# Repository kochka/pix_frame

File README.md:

# pix-frame

A 16×16 pixel art frame that plays retro animations, with the time, the
weather and the room temperature in between. It runs on an ESP32-C6 with a
firmware written in Rust.

▶️ **[Watch the demo on YouTube](https://www.youtube.com/watch?v=8LqMPComf-A)**

## What it does

- Plays your pixel art animations in random order, without showing the same
  one again too soon.
- Every few animations, shows an information screen:
  - the time, set from the internet;
  - the outdoor weather, with an icon and the temperature;
  - the room temperature and humidity.
- Follows the light in the room, dimmer in the evening and brighter in
  daylight.
- Works without Wi-Fi too: it then only plays animations and shows the
  indoor screens.

Everything is in this repository: the firmware, the PC tools, the carrier
board (KiCad) and the 3D-printed rear structure.

## How it works

Animations are authored in the usual formats (GIF, APNG, WebP, PNG), converted
on a PC into a small purpose-built binary format called **PXA**, and streamed
by the firmware from flash with a fixed, predictable memory footprint. The
ESP32 never decodes GIF or PNG.

```text
GIF / APNG / WebP / PNG
          │
          ▼
   pxa convert (PC)
          │
          ▼
    animation.pxa
          │
          ▼
    pxa bundle (PC)  ──►  animations partition  ──►  ESP32-C6 firmware  ──►  WS2815 LED matrix
```

## Hardware

The current frame is:

- an ESP32-C6-WROOM-1-N8 module (8 MB flash, Wi-Fi);
- a 16×16 WS2815 12 V LED matrix, wired as a single serpentine chain;
- the LED data line on GPIO18 (SPI with DMA), driven directly at 3.3 V;
- a MINI560 buck converter supplying 5 V to the ESP32 side;
- an SHT3x temperature and humidity sensor on I2C;
- a GL5528 photoresistor for the ambient light;
- a push button that runs the LED self-test.

The 16×16 size is a configuration, not a limit. Matrix dimensions and wiring
are declared in one place in the firmware and the file format is dimension
agnostic. See the [hardware reference](doc/wiring.md) for the circuit,
external wiring, carrier PCB and assembly instructions, and
[`hardware/mechanical`](hardware/mechanical/) for the printed parts.

## Repository layout

| Path | Contents |
| --- | --- |
| `crates/pxa-core` | `no_std`, allocation-free implementation of the PXA format, shared by the firmware and the converter |
| `firmware` | ESP32-C6 application built on `esp-hal` |
| `tools/pxa` | Desktop CLI that converts animations to PXA, bundles them and inspects PXA files |
| `tools/pixframe` | Desktop CLI that builds the device configuration image |
| `config.example.toml` | Template for the device configuration |
| `partitions.csv` | Flash partition table: firmware, reserved OTA space, `animations` data partition |
| `doc/PXA_spec.md` | Authoritative specification of the PXA binary format |
| `doc/wiring.md` | Hardware reference: circuit, wiring, PCB, assembly and commissioning |
| `hardware` | KiCad 10 project for the carrier board, and the 3D-printed rear structure in `hardware/mechanical` |

## The PXA format in short

A PXA v1 file is a 16-byte header, a global RGB888 palette of 1 to 256 colors,
then one 8-byte header and one payload per frame. Pixels are palette indices
packed at 1, 2, 4 or 8 bits per pixel depending only on the palette size.
Every frame is complete and has its own duration. There is no compression,
no transparency and no metadata, which keeps the decoder tiny.

A 16×16 animation with 16 colors costs 136 bytes per frame. Five seconds at
20 FPS is about 13 KiB.

Full details, byte layouts and validation rules are in
[`doc/PXA_spec.md`](doc/PXA_spec.md).

## Building

Requirements: a stable Rust toolchain (pinned by `rust-toolchain.toml`, which
also pulls the `riscv32imac-unknown-none-elf` target), and
[`espflash`](https://github.com/esp-rs/espflash) to flash the board.
[`mise`](https://mise.jdx.dev/) is optional but provides the canonical tasks.

Host-side checks (format, tests, lints, converter build):

```bash
mise run check
```

Or with plain Cargo:

```bash
cargo test -p pxa-core -p pxa
cargo clippy -p pxa-core -p pxa --all-targets -- -D warnings
cargo build -p pxa --release
```

Firmware:

```bash
mise run build-firmware
# or
cargo build -p pix-frame-firmware --release --target riscv32imac-unknown-none-elf
```

Flash and open the serial monitor. The `espflash` runner in
`.cargo/config.toml` applies `partitions.csv`, so run this from the workspace
root:

```bash
mise run flash
# or
cargo run -p pix-frame-firmware --release --target riscv32imac-unknown-none-elf
```

A plain `cargo build` at the workspace root only builds the host packages; the
firmware always needs the explicit `-p` and `--target`.

### Loading animations onto the frame

Animations live in the `animations` partition, separate from the firmware,
as a bundle of PXA files (see the spec, section 4). Put your `.pxa` files in
`assets/` (ignored by git) and run:

```bash
mise run flash-assets
```

This builds the bundle with `pxa bundle assets/*.pxa -o target/animations.bin`,
erases the partition and writes the image at its offset with `espflash`.
Reflashing the firmware does not touch the animations, and vice versa.

### Configuring the frame

Optional features (information screens, Wi-Fi, clock, weather, ambient
light, display settings) are driven by a configuration stored in the `nvs` partition. Copy
`config.example.toml` to `config.toml` (ignored by git, it holds the Wi-Fi
password), edit it, then:

```bash
mise run flash-config
```

This runs `pixframe config build config.toml -o target/nvs.bin` and writes the
image at the partition offset. `pixframe config dump target/nvs.bin` prints
what an image contains, without the password. A frame without configuration
just plays animations.

### Firmware behavior

At boot the firmware reads the partition table, indexes the bundle (up to 256
animations) and logs what it found over the serial port, including a warning
when indexing stopped before the end of the bundle. It then plays in a
random order: each cycle is a shuffle of every animation, and the first third
of a new cycle never repeats the last third of the previous one, so at least
a third of the catalog plays between two showings of the same animation. An animation loops until at least
`min_play_seconds` (3 by default) have been scheduled at a loop boundary, so short loops repeat and long
ones play once in full.

Frames are scheduled on cumulative deadlines from the first frame: the next
frame is decoded while the current one is displayed, then sent when its
predecessor's duration has elapsed. Decoding and LED transmission time do not
accumulate as drift. A late frame is shown as soon as it is ready and the
schedule is not rebased.

Pressing the BOOT button of the dev board (GPIO9) runs the LED self-test once,
after which playback resumes with the next animation. The self-test ends with
a preview of every screen: text, clock, the seven weather icons in quick
succession, the indoor temperature and humidity screens, and the Wi-Fi
status.

With a `[wifi]` section in the configuration, the firmware joins the network
at boot and keeps reconnecting after drops. The first result is flashed on the
matrix for a moment ("WIFI" then "OK" in green or "KO" in red), and the
self-test ends with the same screen. Once connected, the clock is set from
`pool.ntp.org` and refreshed every hour. The local offset comes from the
configured time zone: built-in rules cover the European Union and UTC, and
the weather service supplies the exact offset for any zone once it has
answered. Without Wi-Fi the frame only plays animations.

With a `[location]` section, the current outdoor conditions are fetched from
[Open-Meteo](https://open-meteo.com/) (free, no key, plain HTTP) every
15 minutes. The weather screen shows an icon for the sky condition (clear,
partly cloudy, cloudy, fog, rain, snow, thunderstorm) above the temperature
in whole degrees, colored from blue to red. It is skipped when the last
answer is older than an hour.

An SHT3x sensor on I2C (SDA on GPIO6, SCL on GPIO7, see `doc/wiring.md`
section 8) is read every minute. Two screens show it: a thermometer above
the temperature, to the tenth of a degree, and a drop above the relative
humidity. They need neither Wi-Fi nor the clock, and are skipped when no
reading succeeded in the last 5 minutes, so a frame without the sensor simply
never shows them.

A GL5528 photoresistor on GPIO2 (see `doc/wiring.md` section 7) is sampled
continuously and its voltage logged every 10 seconds. With a `[light]`
section, the brightness follows the room: the voltage is mapped linearly from
`dark_mv..bright_mv` onto `min_brightness..max_brightness`, and the matrix
moves towards the new value one level every 25 ms instead of jumping. Read
the two thresholds from the logs with the frame assembled in its place: one
in the evening light where the frame should be at its dimmest, one in the
light where it should be at its brightest. Without the section the brightness
stays fixed.

When `info_every` is set, an information screen is shown for 5 seconds after
that many animations. Each screen has an availability condition, so it is
skipped until its data exists: the clock waits for the first time sync, the
weather for the first Open-Meteo answer, the indoor screens for the first
sensor reading. Available screens alternate. Hours are drawn above minutes in
large bold digits, pink above cyan unless `[clock]` sets other colors, with
a separator blinking every second between them. Temperatures are shown in
Celsius, or in Fahrenheit with `temperature_unit = "F"`.

Files whose dimensions differ from the matrix, or that fail validation, are
logged and skipped. Without any playable animation the LED self-test runs
instead. The fixed brightness is a constant at the top of `firmware/src/main.rs`.

## Using the `pxa` converter

The binary is produced at `target/release/pxa`. It has four commands.

### `pxa convert`

Converts one or more source animations to PXA. Supported inputs: GIF, PNG,
APNG and WebP. Each output takes the input's name with a `.pxa` extension.

```bash
pxa convert cat.gif
```

```text
cat.gif -> cat.pxa: 16x16, 12 frames, 9 colors (4 bpp), 1675 bytes
```

Several inputs are converted in turn. A file that fails is reported and
skipped, the others are still written, and the exit status is non-zero. Inputs
that would share an output name, such as `cat.gif` and `cat.png`, are rejected
up front:

```bash
pxa convert *.gif -o animations/
```

Options:

| Option | Effect |
| --- | --- |
| `-o, --output PATH` | Output file for a single input, or an existing directory for any number of inputs. Default: next to each input. |
| `--size WxH` | Resize with nearest-neighbour sampling, e.g. `--size 16x16`. By default the source dimensions are kept. |
| `--background RRGGBB` | Color composited under transparent pixels. Default `000000` (black). |
| `--default-duration MS` | Duration given to source frames whose delay is zero, and to static images. Without it, zero-delay frames are omitted. |
| `--colors N` | Maximum palette size, 1 to 256. Sources with more colors are quantized. Default 256. |

The converter keeps the exact source colors whenever the whole animation fits
the palette, which is the case for almost all pixel art. Quantization only
happens when it must, and a note is printed when it does.

Typical cases:

```bash
# 32×32 source scaled down to the frame, transparent areas over dark grey
pxa convert ghost.png --size 16x16 --background 202020

# Old GIF where every frame has a delay of 0: keep the frames at 100 ms each
pxa convert old.gif --default-duration 100

# Force a 16-color palette (4 bpp) to halve the file size
pxa convert photo.webp --colors 16 -o /tmp/photo16.pxa
```

Two conversions of the same input with the same options produce identical
files.

### `pxa inspect`

Prints the header, the palette and every frame with its duration.

```bash
pxa inspect cat.pxa
```

```text
file:        cat.pxa (439 bytes)
magic:       PXA1
size:        16x16
frames:      3
palette:     5 colors
depth:       4 bpp
payload:     128 bytes per frame
expected:    439 bytes
palette:
    0: #FF0000
    1: #000000
    ...
frames:
     0:   100 ms, 128 payload bytes
     1:   200 ms, 128 payload bytes
     2:    50 ms, 128 payload bytes
total:       350 ms per loop
```

### `pxa bundle`

Validates PXA files and concatenates them, in the given order, into the raw
image expected by the `animations` partition. The image ends with a four-byte
marker so the firmware stops at the last file even if the partition previously
held a larger bundle. Any invalid input aborts the bundle. Files whose dimensions differ from the
rest of the bundle are reported, since the firmware skips them.

```bash
pxa bundle assets/*.pxa -o animations.bin
```

```text
0x000000     3871 bytes  16x16, 14 frames  assets/batman.pxa
0x000f1f      581 bytes  16x16, 4 frames  assets/bissie.pxa
animations.bin: 2 animations, 4456 bytes
```

Write it to the frame with `mise run flash-assets`, or by hand:

```bash
espflash erase-region --chip esp32c6 0x410000 0x3F0000
espflash write-bin --chip esp32c6 0x410000 animations.bin
```

### `pxa validate`

Checks that a file is a conforming PXA v1 file and exits with a non-zero
status otherwise. Errors name the frame and the field at fault.

```bash
pxa validate cat.pxa
```

```text
cat.pxa: valid PXA v1, 16x16, 3 frames, 5 colors
```

```text
error: broken.pxa: invalid PXA file: frame 2: pixel 17 uses palette index 9, outside the palette
```

## Status

Done:

- PXA v1 specification;
- `pxa-core` encoder, decoder and validation, with byte-exact tests;
- `pxa` converter with `convert` (single or bulk), `bundle`, `inspect` and `validate`;
- firmware PXA player streaming from a dedicated flash partition, random
  playlist with a minimum play time;
- firmware LED self-test with a configurable matrix layout;
- device configuration in NVS with the `pixframe` tool;
- Wi-Fi station, SNTP time synchronisation, clock, outdoor weather and indoor
  temperature and humidity screens shown every N animations.

Not yet:

- `pxa preview`;
- Aseprite and Divoom importers;
- uploading animations to the frame without reflashing.

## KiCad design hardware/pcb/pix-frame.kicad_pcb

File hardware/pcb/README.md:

# Carrier PCB

KiCad 10 project for the pix-frame revision A carrier: **54 × 145 mm**, two
copper layers, **1.6 mm** board thickness. The Waveshare ESP32-C6-DEV-KIT-N8
mounts directly by its castellations. The carrier includes an IRF4905 high-side
switch, MINI560 5 V converter, 1N5819 isolation diode, flat-tab DC jack and
matrix/sensor/switch wire-solder pads. C1 and Q1 mount horizontally.

The [hardware reference](../../doc/wiring.md) documents component values,
pad assignments, module polarities, mechanical dimensions and commissioning.

Open the project from the repository root:

```bash
kicad hardware/pcb/pix-frame.kicad_pro
```

| File | Contents |
| --- | --- |
| `pix-frame.kicad_sch` | Electrical schematic |
| `pix-frame.kicad_pcb` | Routed carrier with filled GND planes |
| `pix-frame.kicad_pro` | Net classes and design rules |
| `pixframe.kicad_sym` | Devkit and MINI560 symbols |
| `pixframe.pretty/` | Module, horizontal capacitor, DC jack and wire-pad footprints |
| `pixframe.3dshapes/` | Component models for the KiCad 3D viewer |
| `fp-lib-table`, `sym-lib-table` | Project-local library registrations using `${KIPRJMOD}` |

Generated review files belong in `target/pcb/revA/` at the repository root.
Fabrication outputs belong in `hardware/pcb/production/`. Both directories,
local editor state and backups are ignored by Git. Refill zones, save and
run ERC/DRC with schematic parity before regenerating outputs.

Printable parts and their CAD sources belong in [../mechanical/](../mechanical/).

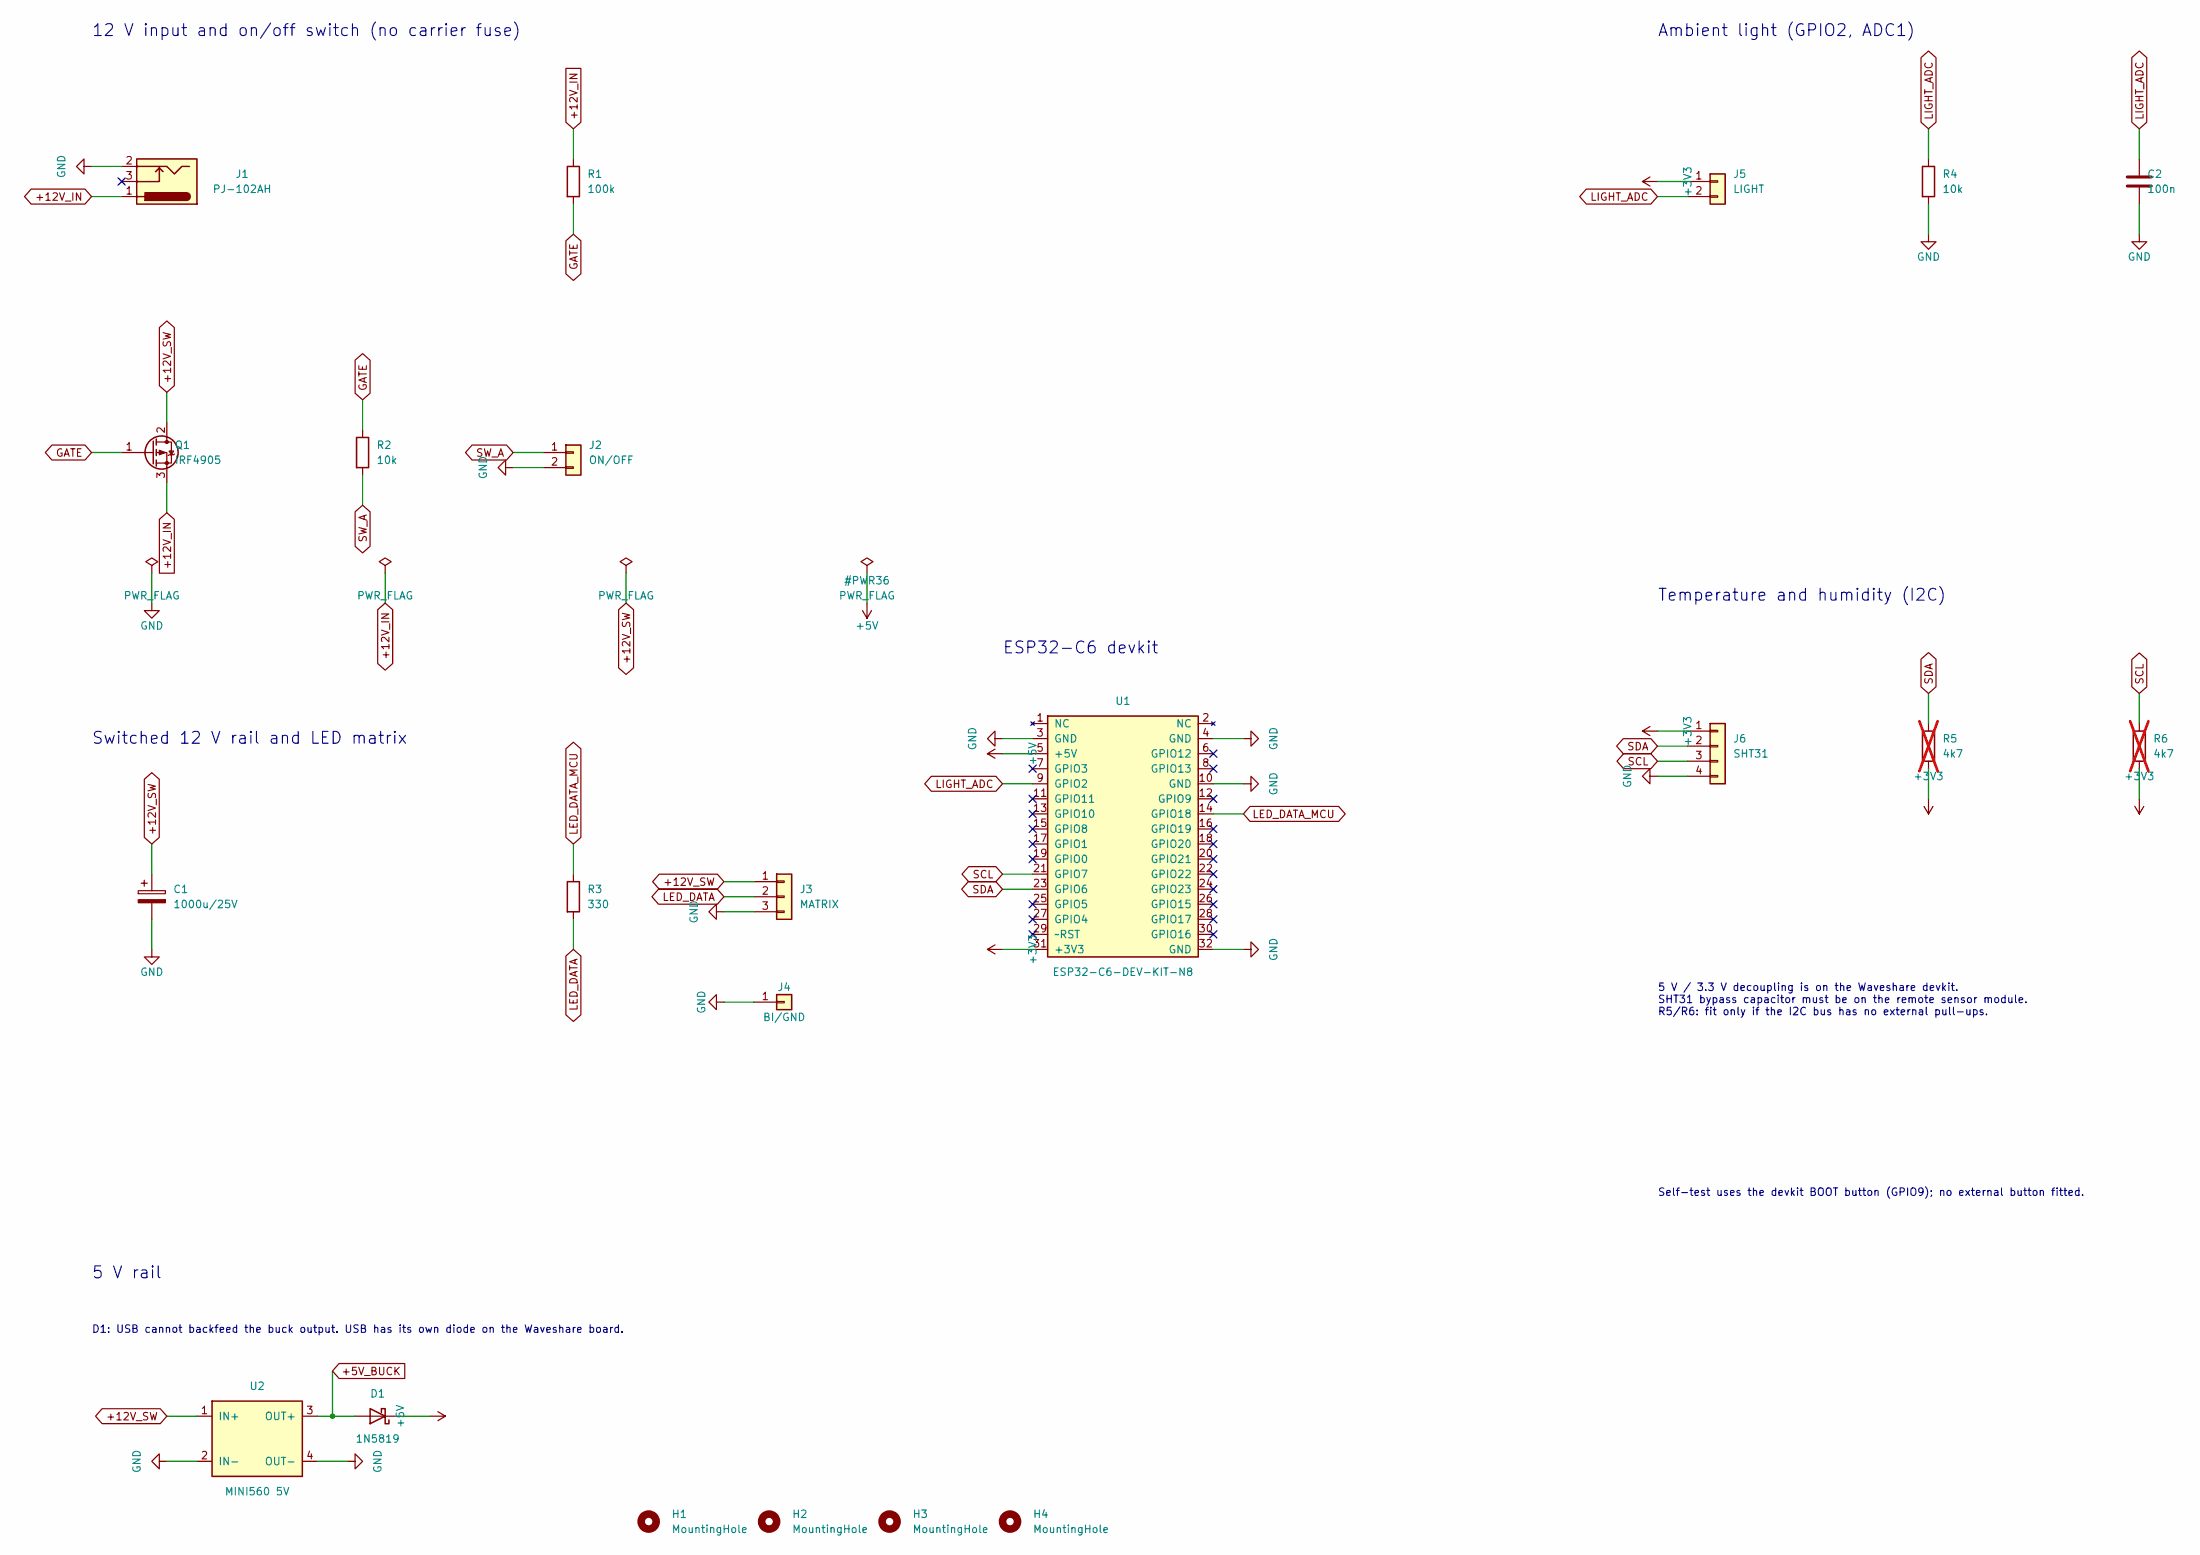
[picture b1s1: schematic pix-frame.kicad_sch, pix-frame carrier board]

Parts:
C1: 1000u/25V; CP_Radial_D10.5mm_L26mm_P5.00mm_Horizontal
C2: 100n; C_Disc_D5.0mm_W2.5mm_P5.00mm
D1: 1N5819; D_DO-41_SOD81_P10.16mm_Horizontal
H1, H2, H3, H4: MountingHole; MountingHole_3.2mm_M3
J1: PJ-102AH; BarrelJack_PJ102AH_Horizontal
J2: ON/OFF; WirePads_2_P4.00mm
J3: MATRIX; WirePads_Matrix_P6.00mm
J4: BI/GND; WirePad_D2.8mm_Drill1.1mm
J5: LIGHT; WirePads_2_P4.00mm
J6: SHT31; WirePads_4_P4.00mm
Q1: IRF4905; TO-220-3_Horizontal_TabUp
R1: 100k; R_Axial_DIN0207_L6.3mm_D2.5mm_P10.16mm_Horizontal
R2, R4: 10k; R_Axial_DIN0207_L6.3mm_D2.5mm_P10.16mm_Horizontal
R3: 330; R_Axial_DIN0207_L6.3mm_D2.5mm_P10.16mm_Horizontal
R5, R6: 4k7; R_Axial_DIN0207_L6.3mm_D2.5mm_P10.16mm_Horizontal; not fitted
U1: ESP32-C6-DEV-KIT-N8; ESP32-C6-DEV-KIT_Waveshare_Castellated
U2: MINI560 5V; MINI560_Buck_22.5x17mm_CornerLands

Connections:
+3V3: J5.1, J6.1, R5.2, R6.2, U1.31 (+3V3)
+5V: D1.1 (K), U1.5 (+5V)
+5V_BUCK: D1.2 (A), U2.3 (OUT+)
+12V_IN: J1.1, Q1.3 (S), R1.1
+12V_SW: C1.1, J3.1, Q1.2 (D), U2.1 (IN+)
GATE: Q1.1 (G), R1.2, R2.1
GND: C1.2, C2.2, J1.2, J2.2, J3.3, J4.1, J6.4, R4.2, U1.3 (GND), U1.4 (GND), U1.10 (GND), U1.32 (GND), U2.2 (IN-), U2.4 (OUT-)
LED_DATA: J3.2, R3.2
LED_DATA_MCU: R3.1, U1.14 (GPIO18)
LIGHT_ADC: C2.1, J5.2, R4.1, U1.9 (GPIO2)
SCL: J6.3, R6.1, U1.21 (GPIO7)
SDA: J6.2, R5.1, U1.23 (GPIO6)
SW_A: J2.1, R2.2

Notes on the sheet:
5 V rail
Switched 12 V rail and LED matrix
D1: USB cannot backfeed the buck output. USB has its own diode on the Waveshare board.
ESP32-C6 devkit
Self-test uses the devkit BOOT button (GPIO9); no external button fitted.
5 V / 3.3 V decoupling is on the Waveshare devkit. SHT31 bypass capacitor must be on the remote sensor module. R5/R6: fit only if the I2C bus has no external pull-ups.
Ambient light (GPIO2, ADC1)
Temperature and humidity (I2C)
12 V input and on/off switch (no carrier fuse)

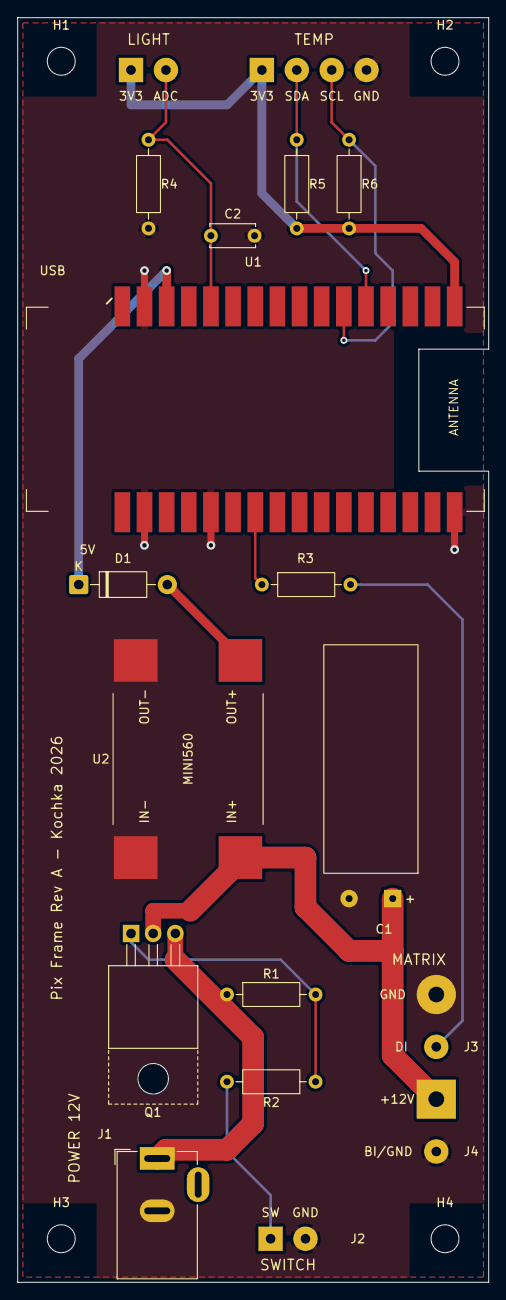
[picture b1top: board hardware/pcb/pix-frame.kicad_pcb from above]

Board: 2 copper layers, 54.0 x 145.0 mm, 22 parts (0 on the bottom side), 13 nets.

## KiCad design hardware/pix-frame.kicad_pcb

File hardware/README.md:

# Hardware

- [`pcb/`](pcb/): KiCad carrier-board project, symbols, footprints and component
  models for the PCB's 3D view.
- [`mechanical/`](mechanical/): CAD sources and printable parts for the frame and
  PCB support.

Open `hardware/pcb/pix-frame.kicad_pro` in KiCad from the workspace root.
See the [hardware reference](../doc/wiring.md) for the circuit, wiring,
carrier dimensions, assembly and commissioning.

Version the design sources and required project libraries. Generated review
files belong under `target/pcb/`; fabrication exports belong under
`hardware/pcb/production/`. Both output directories, local editor state,
backups and Fabrication Toolkit preferences are ignored by Git.

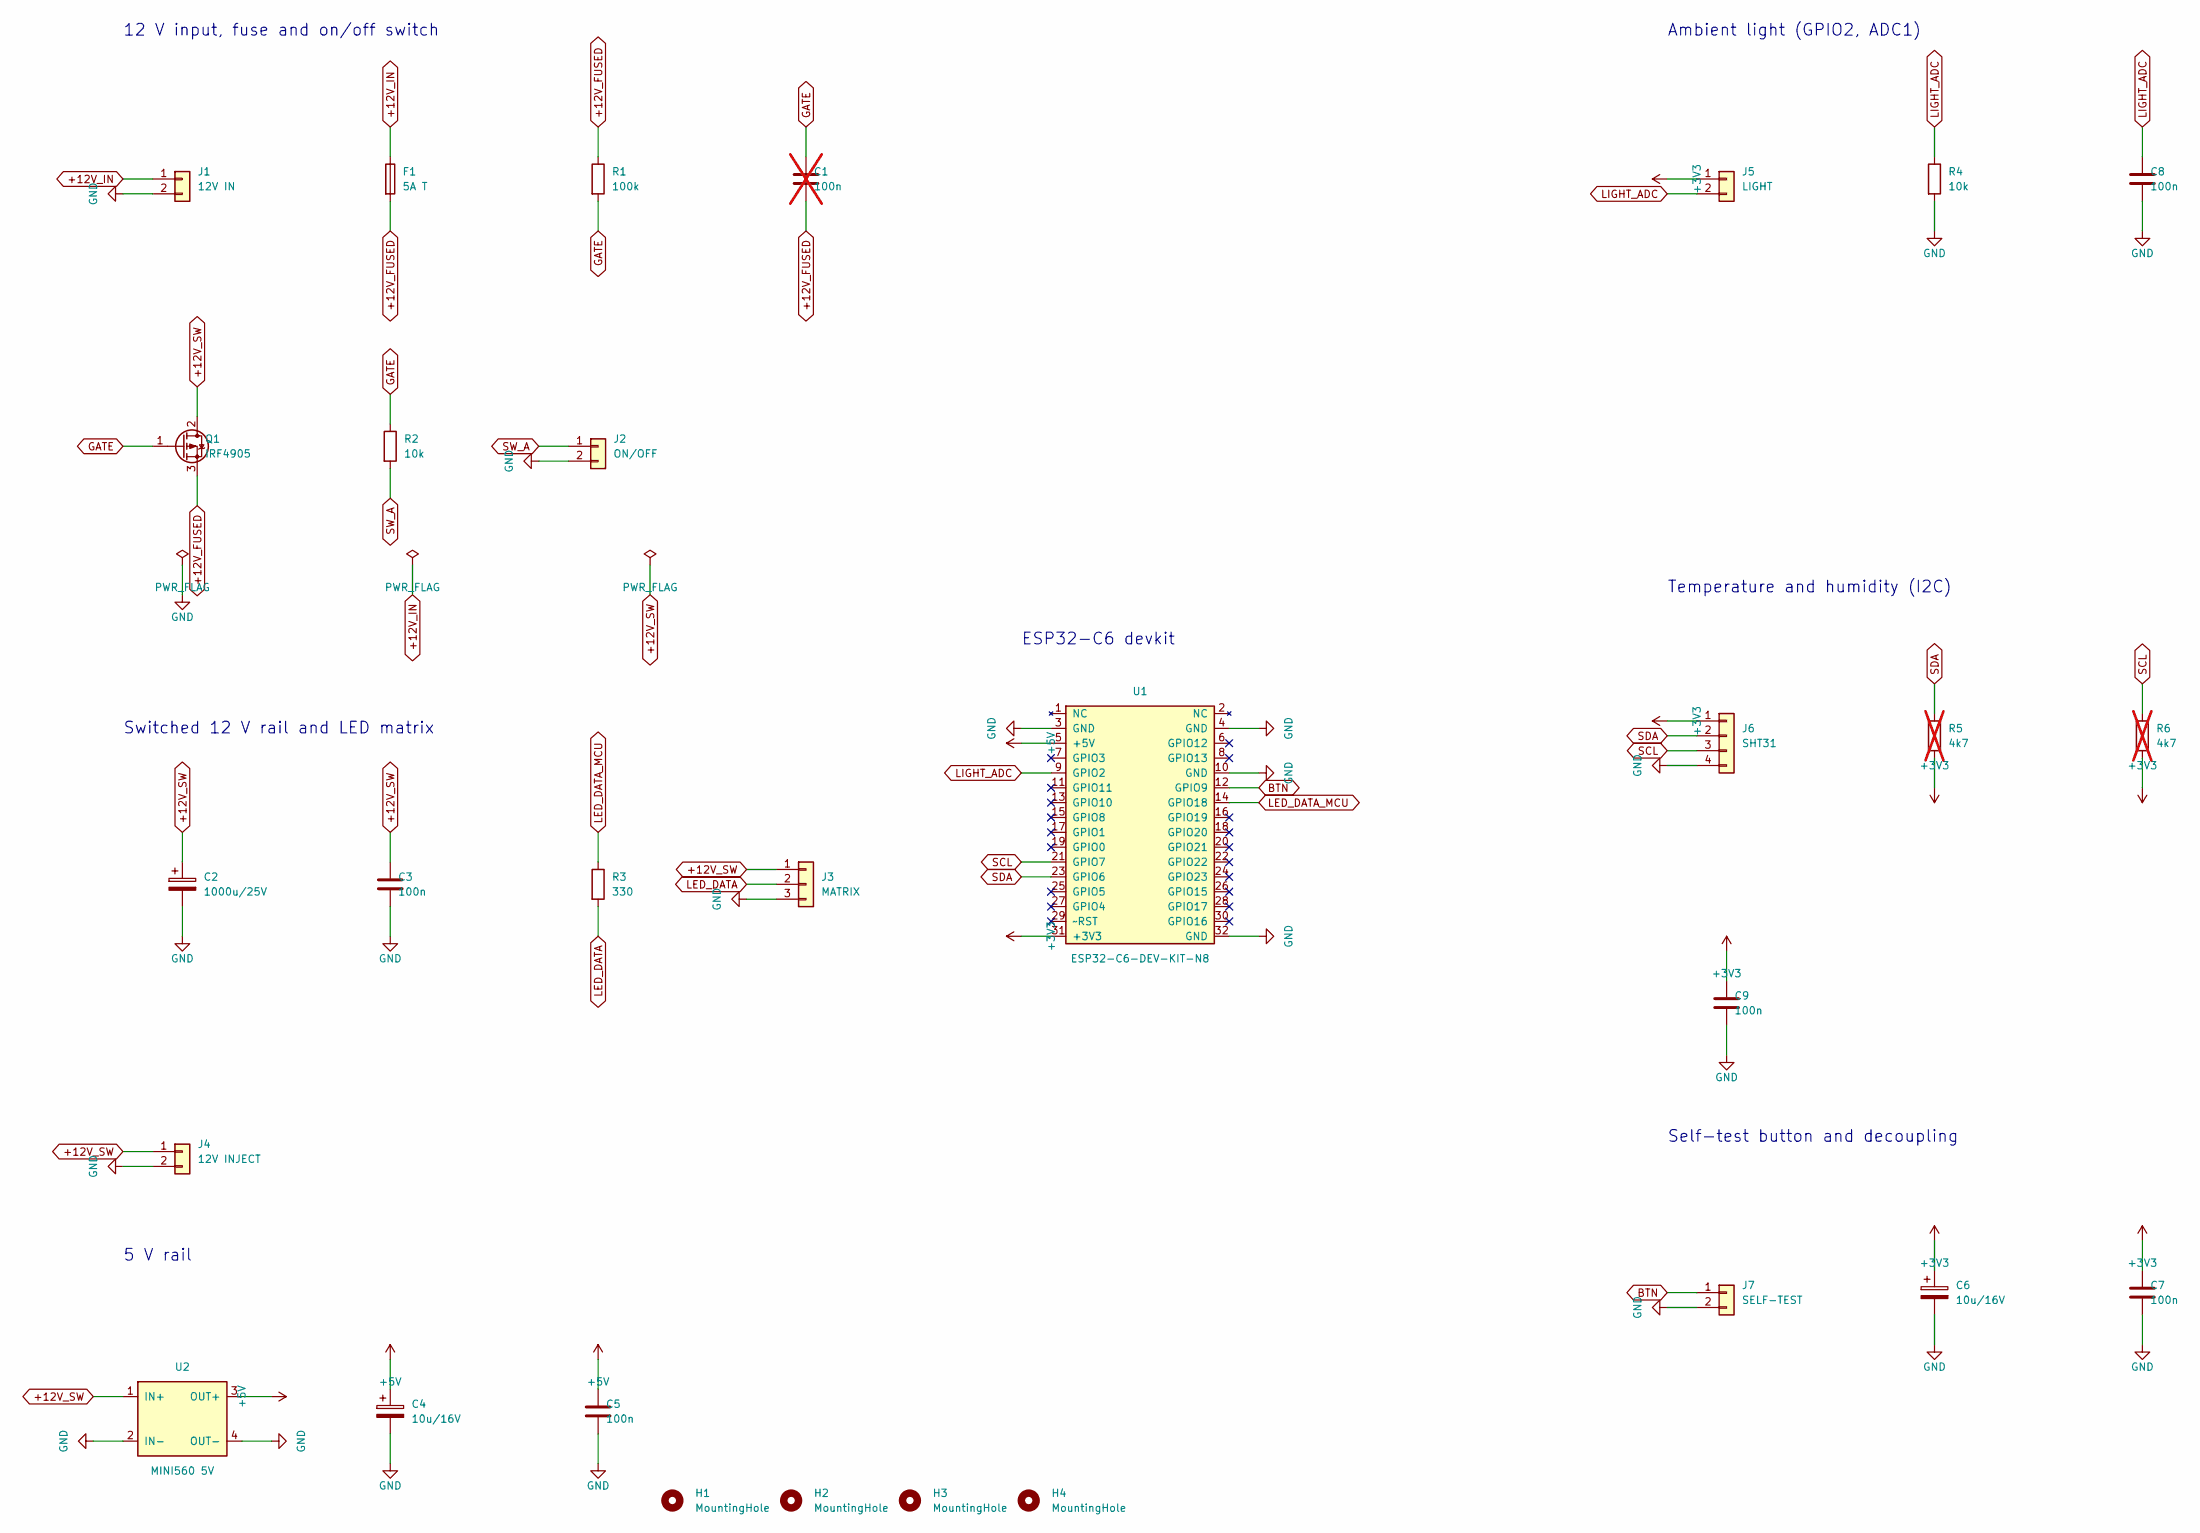
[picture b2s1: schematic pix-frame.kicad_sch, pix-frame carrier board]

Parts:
C1: 100n; C_Disc_D5.0mm_W2.5mm_P5.00mm; not fitted
C2: 1000u/25V; CP_Radial_D10.0mm_P5.00mm
C3, C5, C7, C8, C9: 100n; C_Disc_D5.0mm_W2.5mm_P5.00mm
C4, C6: 10u/16V; CP_Radial_D5.0mm_P2.50mm
F1: 5A T; Fuseholder_Clip-5x20mm_Keystone_3517_Inline_P23.11x6.76mm_D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
H1, H2, H3, H4: MountingHole; MountingHole_3.2mm_M3
J1: 12V IN; TerminalBlock_MaiXu_MX126-5.0-02P_1x02_P5.00mm
J2: ON/OFF; PinHeader_1x02_P2.54mm_Vertical
J3: MATRIX; TerminalBlock_MaiXu_MX126-5.0-03P_1x03_P5.00mm
J4: 12V INJECT; TerminalBlock_MaiXu_MX126-5.0-02P_1x02_P5.00mm
J5: LIGHT; PinHeader_1x02_P2.54mm_Vertical
J6: SHT31; PinHeader_1x04_P2.54mm_Vertical
J7: SELF-TEST; PinHeader_1x02_P2.54mm_Vertical
Q1: IRF4905; TO-220-3_Vertical
R1: 100k; R_Axial_DIN0207_L6.3mm_D2.5mm_P10.16mm_Horizontal
R2, R4: 10k; R_Axial_DIN0207_L6.3mm_D2.5mm_P10.16mm_Horizontal
R3: 330; R_Axial_DIN0207_L6.3mm_D2.5mm_P10.16mm_Horizontal
R5, R6: 4k7; R_Axial_DIN0207_L6.3mm_D2.5mm_P10.16mm_Horizontal; not fitted
U1: ESP32-C6-DEV-KIT-N8; ESP32-C6-DEV-KIT_Waveshare_2x16_P2.54mm
U2: MINI560 5V; MINI560_Buck_29x18mm

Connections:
+3V3: C6.1, C7.1, C9.1, J5.1, J6.1, R5.2, R6.2, U1.31 (+3V3)
+5V: C4.1, C5.1, U1.5 (+5V), U2.3 (OUT+)
+12V_FUSED: C1.2, F1.2, Q1.3 (S), R1.1
+12V_IN: F1.1, J1.1
+12V_SW: C2.1, C3.1, J3.1, J4.1, Q1.2 (D), U2.1 (IN+)
BTN: J7.1, U1.12 (GPIO9)
GATE: C1.1, Q1.1 (G), R1.2, R2.1
GND: C2.2, C3.2, C4.2, C5.2, C6.2, C7.2, C8.2, C9.2, J1.2, J2.2, J3.3, J4.2, J6.4, J7.2, R4.2, U1.3 (GND), U1.4 (GND), U1.10 (GND), U1.32 (GND), U2.2 (IN-), U2.4 (OUT-)
LED_DATA: J3.2, R3.2
LED_DATA_MCU: R3.1, U1.14 (GPIO18)
LIGHT_ADC: C8.1, J5.2, R4.1, U1.9 (GPIO2)
SCL: J6.3, R6.1, U1.21 (GPIO7)
SDA: J6.2, R5.1, U1.23 (GPIO6)
SW_A: J2.1, R2.2

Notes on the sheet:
12 V input, fuse and on/off switch
Switched 12 V rail and LED matrix
5 V rail
Ambient light (GPIO2, ADC1)
Temperature and humidity (I2C)
Self-test button and decoupling
ESP32-C6 devkit

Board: 2 copper layers, 30 parts (0 on the bottom side), 14 nets, no tracks yet.

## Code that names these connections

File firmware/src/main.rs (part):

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    let timg0 = TimerGroup::new(peripherals.TIMG0);
    esp_rtos::start(timg0.timer0, peripherals.FROM_CPU_INTR0);

    // The WS2815 frame is wired to GPIO18; the signal is generated by SPI
    // with DMA so its timing does not depend on the CPU. See `doc/wiring.md`.
    let mut led = match SpiLeds::new(
        peripherals.SPI2,
        peripherals.DMA_CH0,
        peripherals.GPIO18,
        LED_COUNT,
    ) {
        Ok(led) => led,
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
    let delay = Delay::new();
    let mut pixels = [RGB8::new(0, 0, 0); LED_COUNT];
    // Self-test button: GPIO9 is the BOOT button of the Espressif ESP32-C6
    // dev boards, pulled up and low when pressed. Any GPIO with a button to
    // ground works the same way. See `doc/wiring.md` section 6.
    let mut button = Button::new(Input::new(
        peripherals.GPIO9,
        InputConfig::default().with_pull(Pull::Up),
    ));

    // SHT3x temperature and humidity sensor on I2C, SDA on GPIO6 and SCL on
    // GPIO7, 100 kHz. See `doc/wiring.md` section 8.
    match I2c::new(
        peripherals.I2C0,
        I2cConfig::default().with_frequency(Rate::from_khz(100)),
    ) {
        Ok(i2c) => {
            let i2c = i2c
                .with_sda(peripherals.GPIO6)
                .with_scl(peripherals.GPIO7)
                .into_async();
            spawn(&spawner, indoor::indoor_task(i2c), "indoor");
        }
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            Config::default()
        }
    };
    // GL5528 photoresistor divider on GPIO2, which belongs to ADC1: ADC2 is
    // unusable while the radio runs. See `doc/wiring.md` section 7.
    let sensor = light::Sensor::new(peripherals.ADC1, peripherals.GPIO2);
    spawn(&spawner, light::light_task(sensor, config.light), "light");

    let clock = Clock::new(RTC.init(Rtc::new(peripherals.RTC_TIMER)));
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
